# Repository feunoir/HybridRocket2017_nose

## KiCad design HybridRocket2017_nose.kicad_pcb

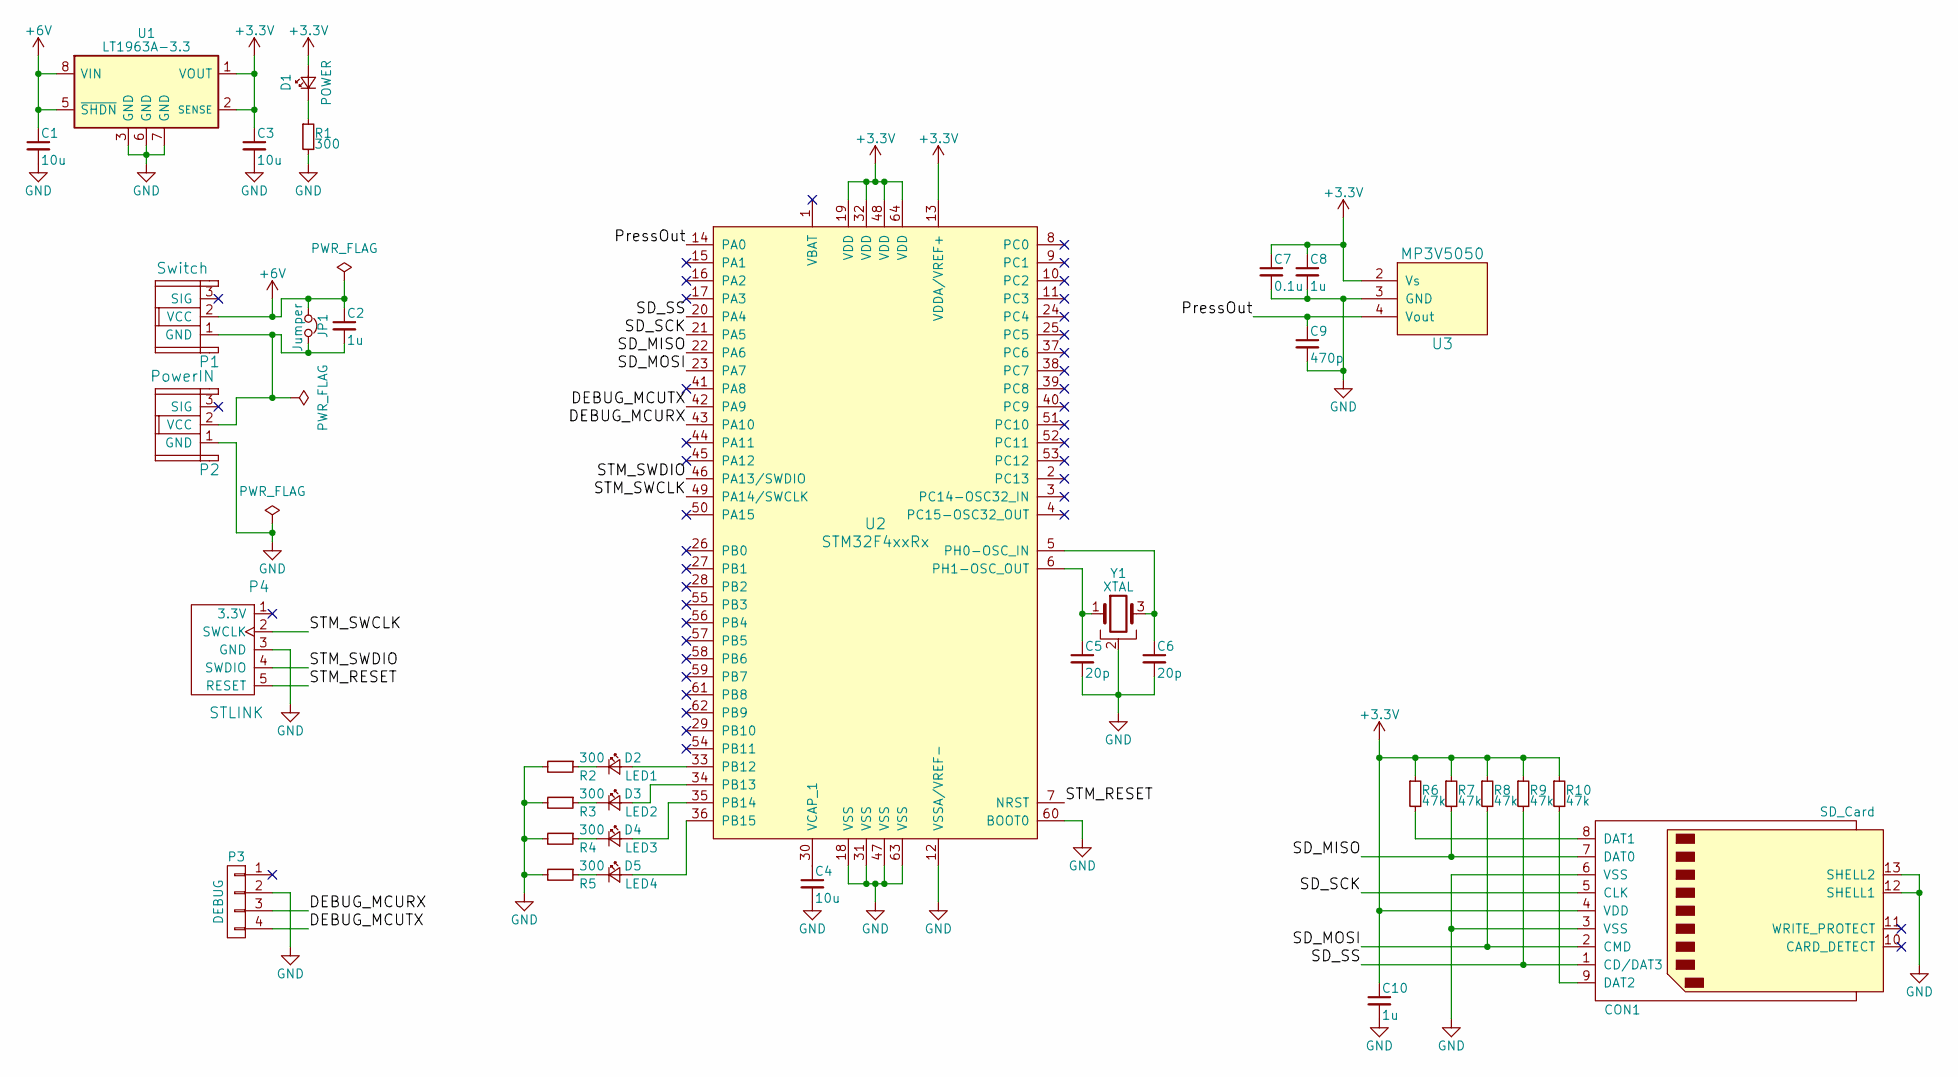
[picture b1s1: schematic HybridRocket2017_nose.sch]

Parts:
C1, C3, C4: 10u; C_0805
C2, C8, C10: 1u; C_0805
C5, C6: 20p; C_0603
C7: 0.1u; C_0603
C9: 470p; C_0603
CON1: SD_Card; microSD_DM3AT-SFPEJ
D1: POWER; LED_0603
D2: LED1; LED_0603
D3: LED2; LED_0603
D4: LED3; LED_0603
D5: LED4; LED_0603
JP1: Jumper; GAP_NC
P1: Switch; DF1E-3P
P2: PowerIN; DF1E-3P
P3: DEBUG; Pin_Header_Straight_1x04_Pitch2.54mm
P4: STLINK; DF1E-5P_Straight
R1, R2, R3, R4, R5: 300; R_0603_HandSoldering
R6, R7, R8, R9, R10: 47k; R_0603_HandSoldering
U1: LT1963A-3.3; SOIC-8_3.9x4.9mm_Pitch1.27mm
U2: STM32F4xxRx; LQFP-64_10x10mm_Pitch0.5mm
U3: MP3V5050
Y1: XTAL; Crystal_HC49-U-3pin_Vertical

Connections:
+3V3: C3.1, C7.1, C8.1, C10.1, CON1.4 (VDD), D1.2 (A), R6.1, R7.1, R8.1, R9.1, R10.1, U1.1 (VOUT), U1.2 (SENSE), U2.13 (VDDA/VREF+), U2.19 (VDD), U2.32 (VDD), U2.48 (VDD), U2.64 (VDD), U3.2 (Vs)
+6V: C1.1, C2.1, JP1.1, P1.2 (VCC), U1.5 (~SHDN), U1.8 (VIN)
/DEBUG_MCURX: P3.3, U2.43 (PA10)
/DEBUG_MCUTX: P3.4, U2.42 (PA9)
/PressOut: C9.1, U2.14 (PA0), U3.4 (Vout)
/SD_MISO: CON1.7 (DAT0), R7.2, U2.22 (PA6)
/SD_MOSI: CON1.2 (CMD), R8.2, U2.23 (PA7)
/SD_SCK: CON1.5 (CLK), U2.21 (PA5)
/SD_SS: CON1.1 (CD/DAT3), R9.2, U2.20 (PA4)
/STM_RESET: P4.5 (RESET), U2.7 (NRST)
/STM_SWCLK: P4.2 (SWCLK), U2.49 (PA14/SWCLK)
/STM_SWDIO: P4.4 (SWDIO), U2.46 (PA13/SWDIO)
GND: C1.2, C3.2, C4.2, C5.2, C6.2, C7.2, C8.2, C9.2, C10.2, CON1.3 (VSS), CON1.6 (VSS), CON1.12 (SHELL1), CON1.13 (SHELL2), P2.1 (GND), P3.2, P4.3 (GND), R1.2, R2.2, R3.2, R4.2, R5.2, U1.3 (GND), U1.6 (GND), U1.7 (GND), U2.12 (VSSA/VREF-), U2.18 (VSS), U2.31 (VSS), U2.47 (VSS), U2.60 (BOOT0), U2.63 (VSS), U3.3 (GND), Y1.2
unnamed: C2.2, JP1.2, P1.1 (GND), P2.2 (VCC)
unnamed: C4.1, U2.30 (VCAP_1)
unnamed: C5.1, U2.6 (PH1-OSC_OUT), Y1.1
unnamed: C6.1, U2.5 (PH0-OSC_IN), Y1.3
unnamed: CON1.8 (DAT1), R6.2
unnamed: CON1.9 (DAT2), R10.2
unnamed: D1.1 (K), R1.1
unnamed: D2.1 (K), R2.1
unnamed: D2.2 (A), U2.33 (PB12)
unnamed: D3.1 (K), R3.1
unnamed: D3.2 (A), U2.34 (PB13)
unnamed: D4.1 (K), R4.1
unnamed: D4.2 (A), U2.35 (PB14)
unnamed: D5.1 (K), R5.1
unnamed: D5.2 (A), U2.36 (PB15)

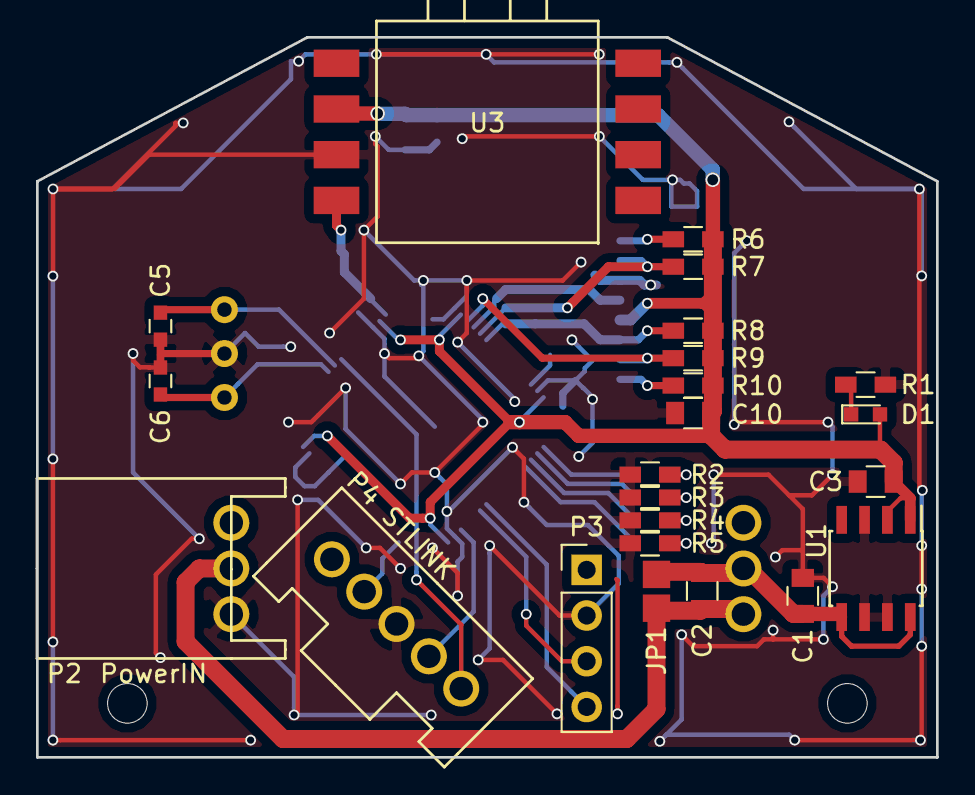
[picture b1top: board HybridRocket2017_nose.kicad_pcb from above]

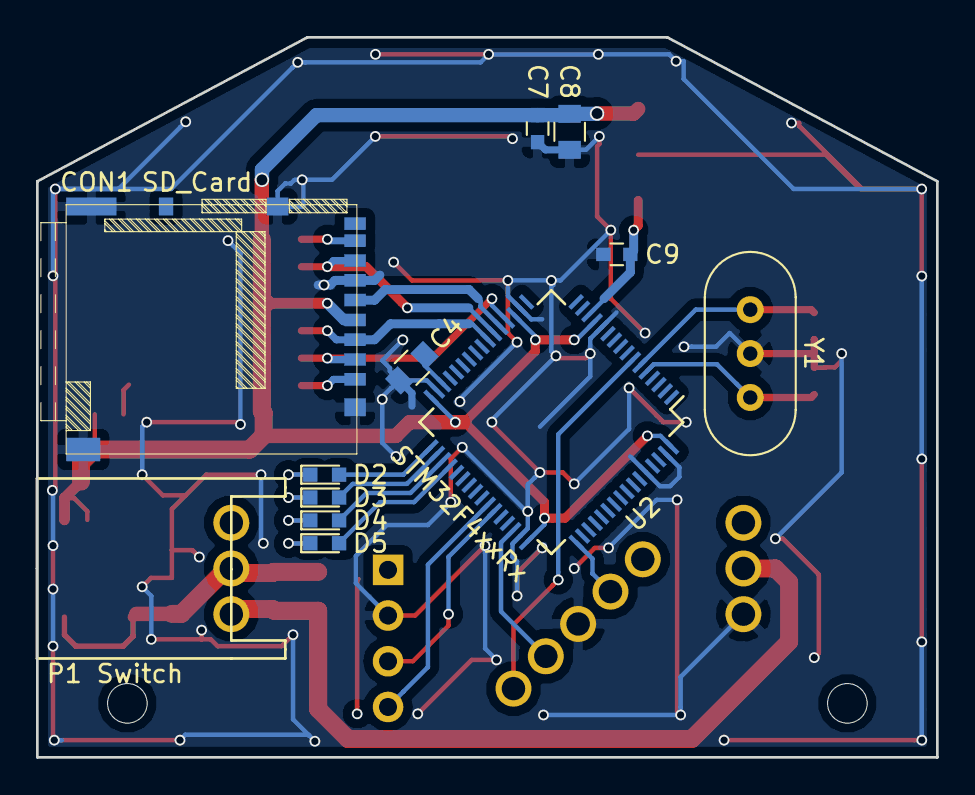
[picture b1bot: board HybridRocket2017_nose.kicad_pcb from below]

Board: 2 copper layers, 50.0 x 40.0 mm, 35 parts (12 on the bottom side), 28 nets.

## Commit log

2017-03-10 :tada: Added .gitattributes & .gitignore files
2017-03-10 firstcommit
2017-07-02 製作中にコミットするの忘れてた
